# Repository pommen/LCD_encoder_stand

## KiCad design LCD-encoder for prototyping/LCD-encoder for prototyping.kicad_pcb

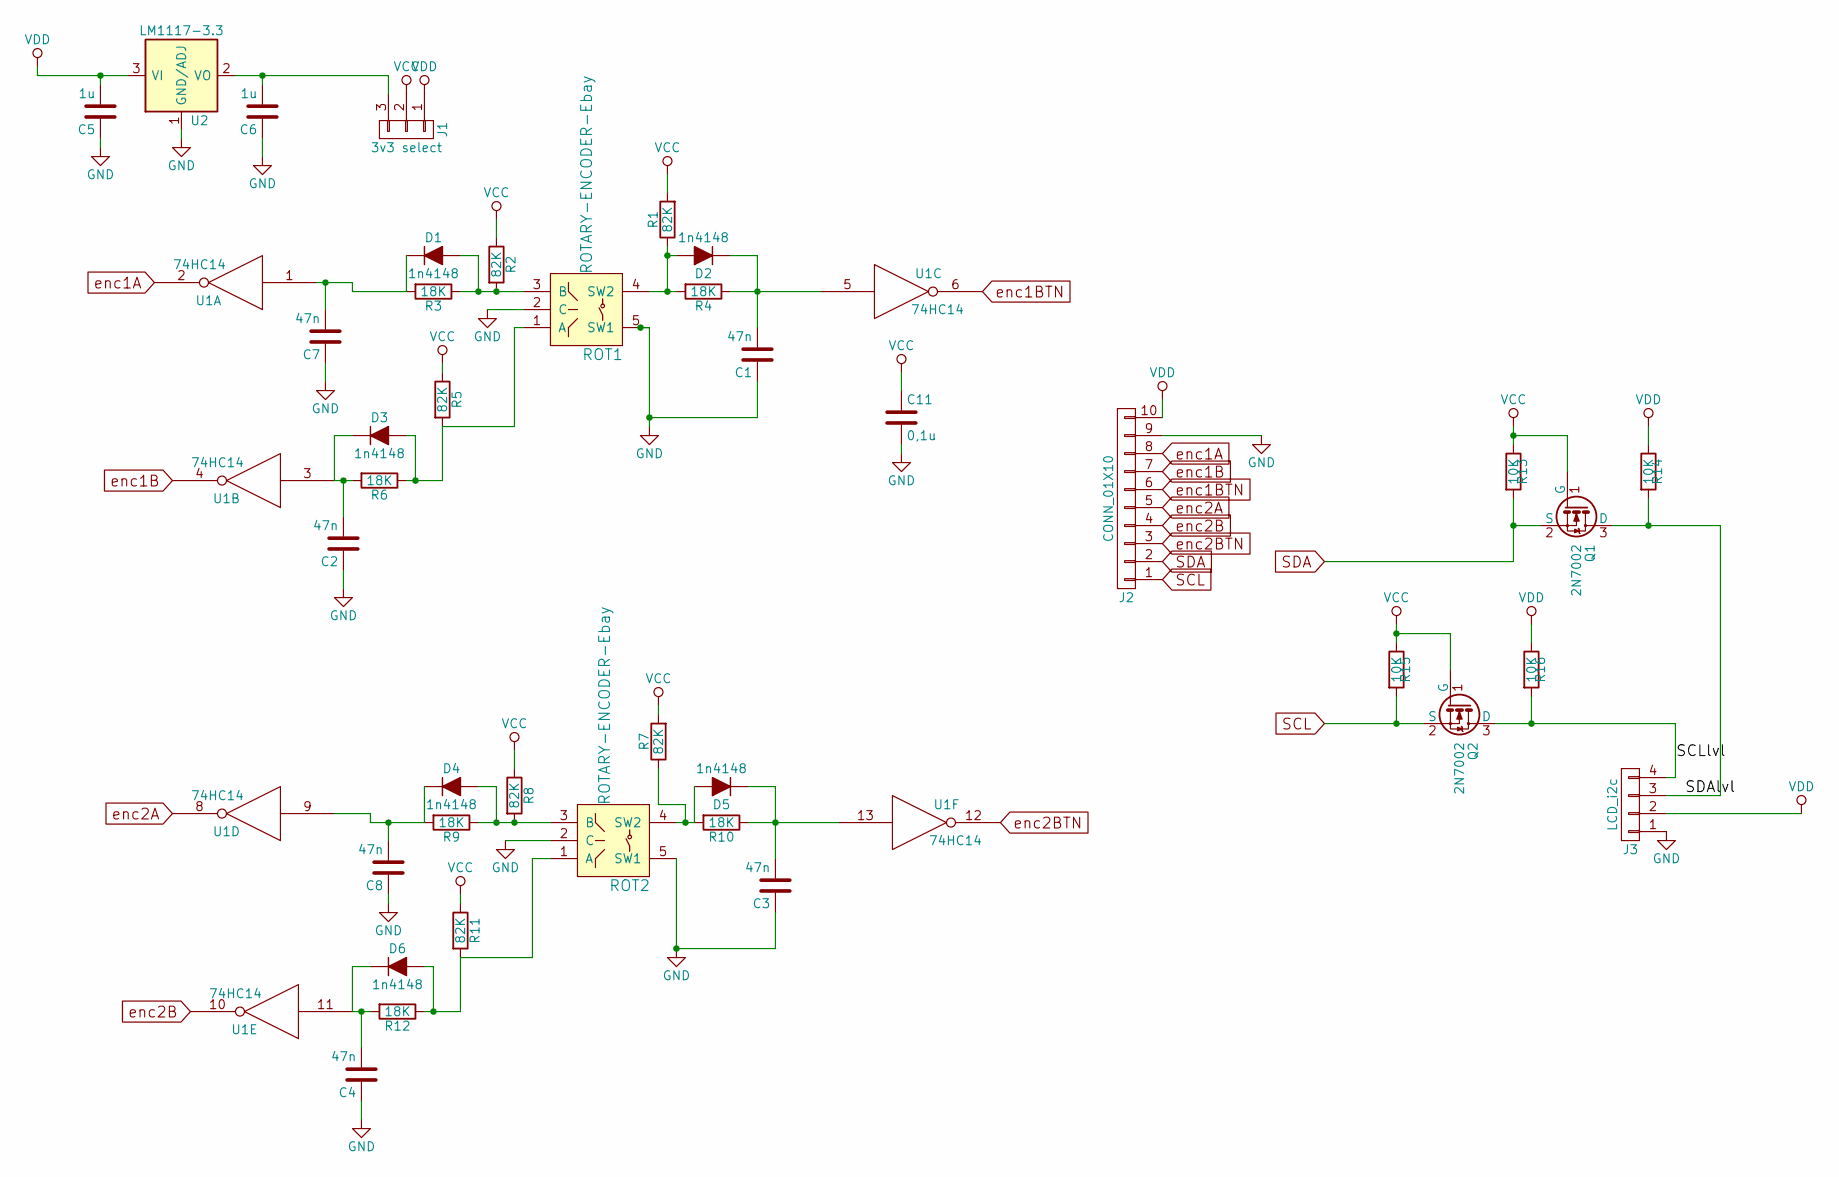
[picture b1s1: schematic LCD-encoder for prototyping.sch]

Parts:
C1, C2, C3, C4, C7, C8: 47n; C_0805_HandSoldering
C5, C6: 1u; C_0805_HandSoldering
C11: 0,1u; C_0805_HandSoldering
D1, D2, D3, D4, D5, D6: 1n4148; D_MiniMELF_Handsoldering
J1: 3v3 select; Pin_Header_Straight_1x03_Pitch2.54mm
J2: CONN_01X10; Pin_Header_Straight_1x10_Pitch2.54mm
J3: LCD_i2c; Pin_Header_Straight_1x04_Pitch2.54mm
Q1, Q2: 2N7002; SOT-23
R1, R2, R5, R7, R8, R11: 82K; C_0805_HandSoldering
R3, R4, R6, R9, R10, R12: 18K; C_0805_HandSoldering
R13, R14, R15, R16: 10K; C_0805_HandSoldering
ROT1, ROT2: ROTARY-ENCODER-Ebay
U1: 74HC14; DIP-14_W7.62mm_LongPads
U2: LM1117-3.3; SOT-223

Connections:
/SCLlvl: J3.4, Q2.3 (D), R16.2
/SDAlvl: J3.3, Q1.3 (D), R14.2
GND: C1.1, C2.1, C3.1, C4.1, C5.1, C6.1, C7.1, C8.1, C11.2, J2.9, J3.1, ROT1.2 (C), ROT1.5 (SW1), ROT2.2 (C), ROT2.5 (SW1), U1.7 (GND), U2.1 (GND/ADJ)
unnamed: C1.2, D2.1 (K), R4.1, U1.5
unnamed: C2.2, D3.1 (K), R6.2, U1.3
unnamed: C3.2, D5.1 (K), R10.1, U1.13
unnamed: C4.2, D6.1 (K), R12.2, U1.11
unnamed: C6.2, J1.3, U2.2 (VO), U2.4 (VO)
unnamed: C7.2, D1.1 (K), R3.2, U1.1
unnamed: C8.2, D4.1 (K), R9.2, U1.9
unnamed: D1.2 (A), R2.2, R3.1, ROT1.3 (B)
unnamed: D2.2 (A), R1.1, R4.2, ROT1.4 (SW2)
unnamed: D3.2 (A), R5.2, R6.1, ROT1.1 (A)
unnamed: D4.2 (A), R8.2, R9.1, ROT2.3 (B)
unnamed: D5.2 (A), R7.1, R10.2, ROT2.4 (SW2)
unnamed: D6.2 (A), R11.2, R12.1, ROT2.1 (A)
SCL: J2.1, Q2.2 (S), R15.2
SDA: J2.2, Q1.2 (S), R13.2
VCC: C11.1, J1.2, Q1.1 (G), Q2.1 (G), R1.2, R2.1, R5.1, R7.2, R8.1, R11.1, R13.1, R15.1, U1.14 (VCC)
VDD: C5.2, J1.1, J2.10, J3.2, R14.1, R16.1, U2.3 (VI)
enc1A: J2.8, U1.2
enc1B: J2.7, U1.4
enc1BTN: J2.6, U1.6
enc2A: J2.5, U1.8
enc2B: J2.4, U1.10
enc2BTN: J2.3, U1.12

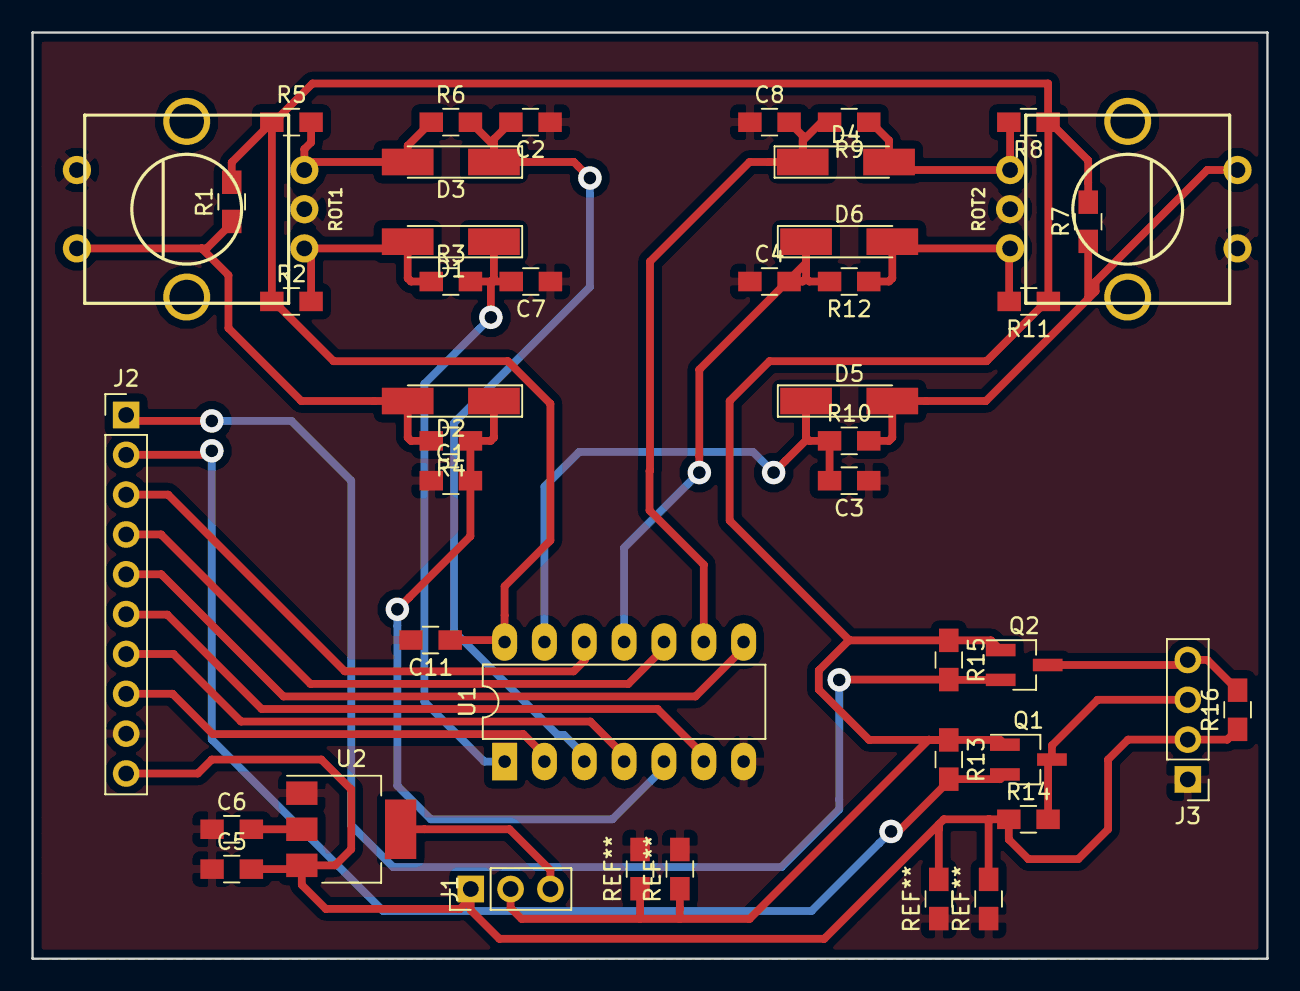
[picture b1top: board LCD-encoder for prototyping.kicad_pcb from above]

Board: 2 copper layers, 78.7 x 59.1 mm, 40 parts (0 on the bottom side), 26 nets.

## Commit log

2017-09-07 Flatcam project
2017-09-07 Pictures
2017-09-07 Mechanical drawing
